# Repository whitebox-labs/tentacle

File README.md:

# Whitebox Labs Tentacle Shield for Arduino
`Models T1.15A, T1.16`

## What's the Tentacle Shield?
An Arduino shield to host and individually isolate up to 4 EZO Circuits from Atlas Scientific to measure PH, Dissolved Oxygen, Electric Conductivity (E.C.), Oxidation-Reduction Potential (ORP) and RTD (Temperature).

* 4 channels
* 5V only

Individually isolated measurement circuits and communication lines prevent noise and ground loops for precise measurements even in closed-loop systems.

## Getting Started
* [Documentation Site](https://www.whiteboxes.ch/docs/tentacle/t1)
* Download the [Setup Sketch](https://raw.githubusercontent.com/whitebox-labs/tentacle-examples/master/arduino/tentacle-setup/tentacle_setup/tentacle_setup.ino)
* [Quick Start Tutorial](https://www.whiteboxes.ch/docs/tentacle/t1/#/quickstart)

## Code Examples
* [Continuous readings](https://www.whiteboxes.ch/docs/tentacle/t1/#/continuous-example)
* [Continuous, asynchronous readings](https://www.whiteboxes.ch/docs/tentacle/t1/#/asynchronous-example)
* [Interactive, bidirectional communications](https://www.whiteboxes.ch/docs/tentacle/t1/#/interactive-example)
* [Examples Git Repository](https://github.com/whitebox-labs/tentacle-examples) `git clone https://github.com/whitebox-labs/tentacle-examples.git`
* [Download all examples (zip)](https://github.com/whitebox-labs/tentacle-examples/archive/master.zip)

## Downloads
* [Tentacle Setup sketch](https://raw.githubusercontent.com/whitebox-labs/tentacle-examples/master/arduino/tentacle-setup/tentacle_setup/tentacle_setup.ino)
* [T1.16 3D-Model (STL)](https://github.com/whitebox-labs/tentacle/blob/master/hardware/mechanical/tentacle_t1.STL)
* [T1.16 3D-Model (STEP)](https://github.com/whitebox-labs/tentacle/blob/master/hardware/mechanical/tentacle_t1.STEP)
* [T1.16 Mechanical Drawing (PDF)](https://github.com/whitebox-labs/tentacle/raw/master/hardware/mechanical/tentacle_t1_mechanical.pdf)
* [BNC Connector Mechanical Drawing (PDF)](https://github.com/whitebox-labs/tentacle/raw/master/hardware/mechanical/bnc_mechanical.pdf)
* [T1.16 Schematic (PDF)](https://github.com/whitebox-labs/tentacle/raw/master/hardware/tentacle_schematic.pdf)

## Support
For customer support, please use the [contact form](https://www.whiteboxes.ch/contact/) on our website.

If you find bug in the documentation, examples or the schematic, feel free to create an issue or even a pull request here on GitHub. 

## Open Source
The Tentacle Shield is [certified](http://certificate.oshwa.org/certification-directory/) Open Source Hardware with UID CH000003. Schematics and layout are licensed under [Creative Commons BY-SA 4.0](http://creativecommons.org/licenses/by-sa/4.0/). Silkscreen graphics and the trade mark “Tentacle” are intellectual property of Whitebox Labs

* [Hardware source files on GitHub](https://github.com/whitebox-labs/tentacle) `git clone https://github.com/whitebox-labs/tentacle.git`

Made with 

## Buy
* From [our store](https://www.whiteboxes.ch/) – we ship worldwide
* or from one of our [Distributors](https://www.whiteboxes.ch/distributors)

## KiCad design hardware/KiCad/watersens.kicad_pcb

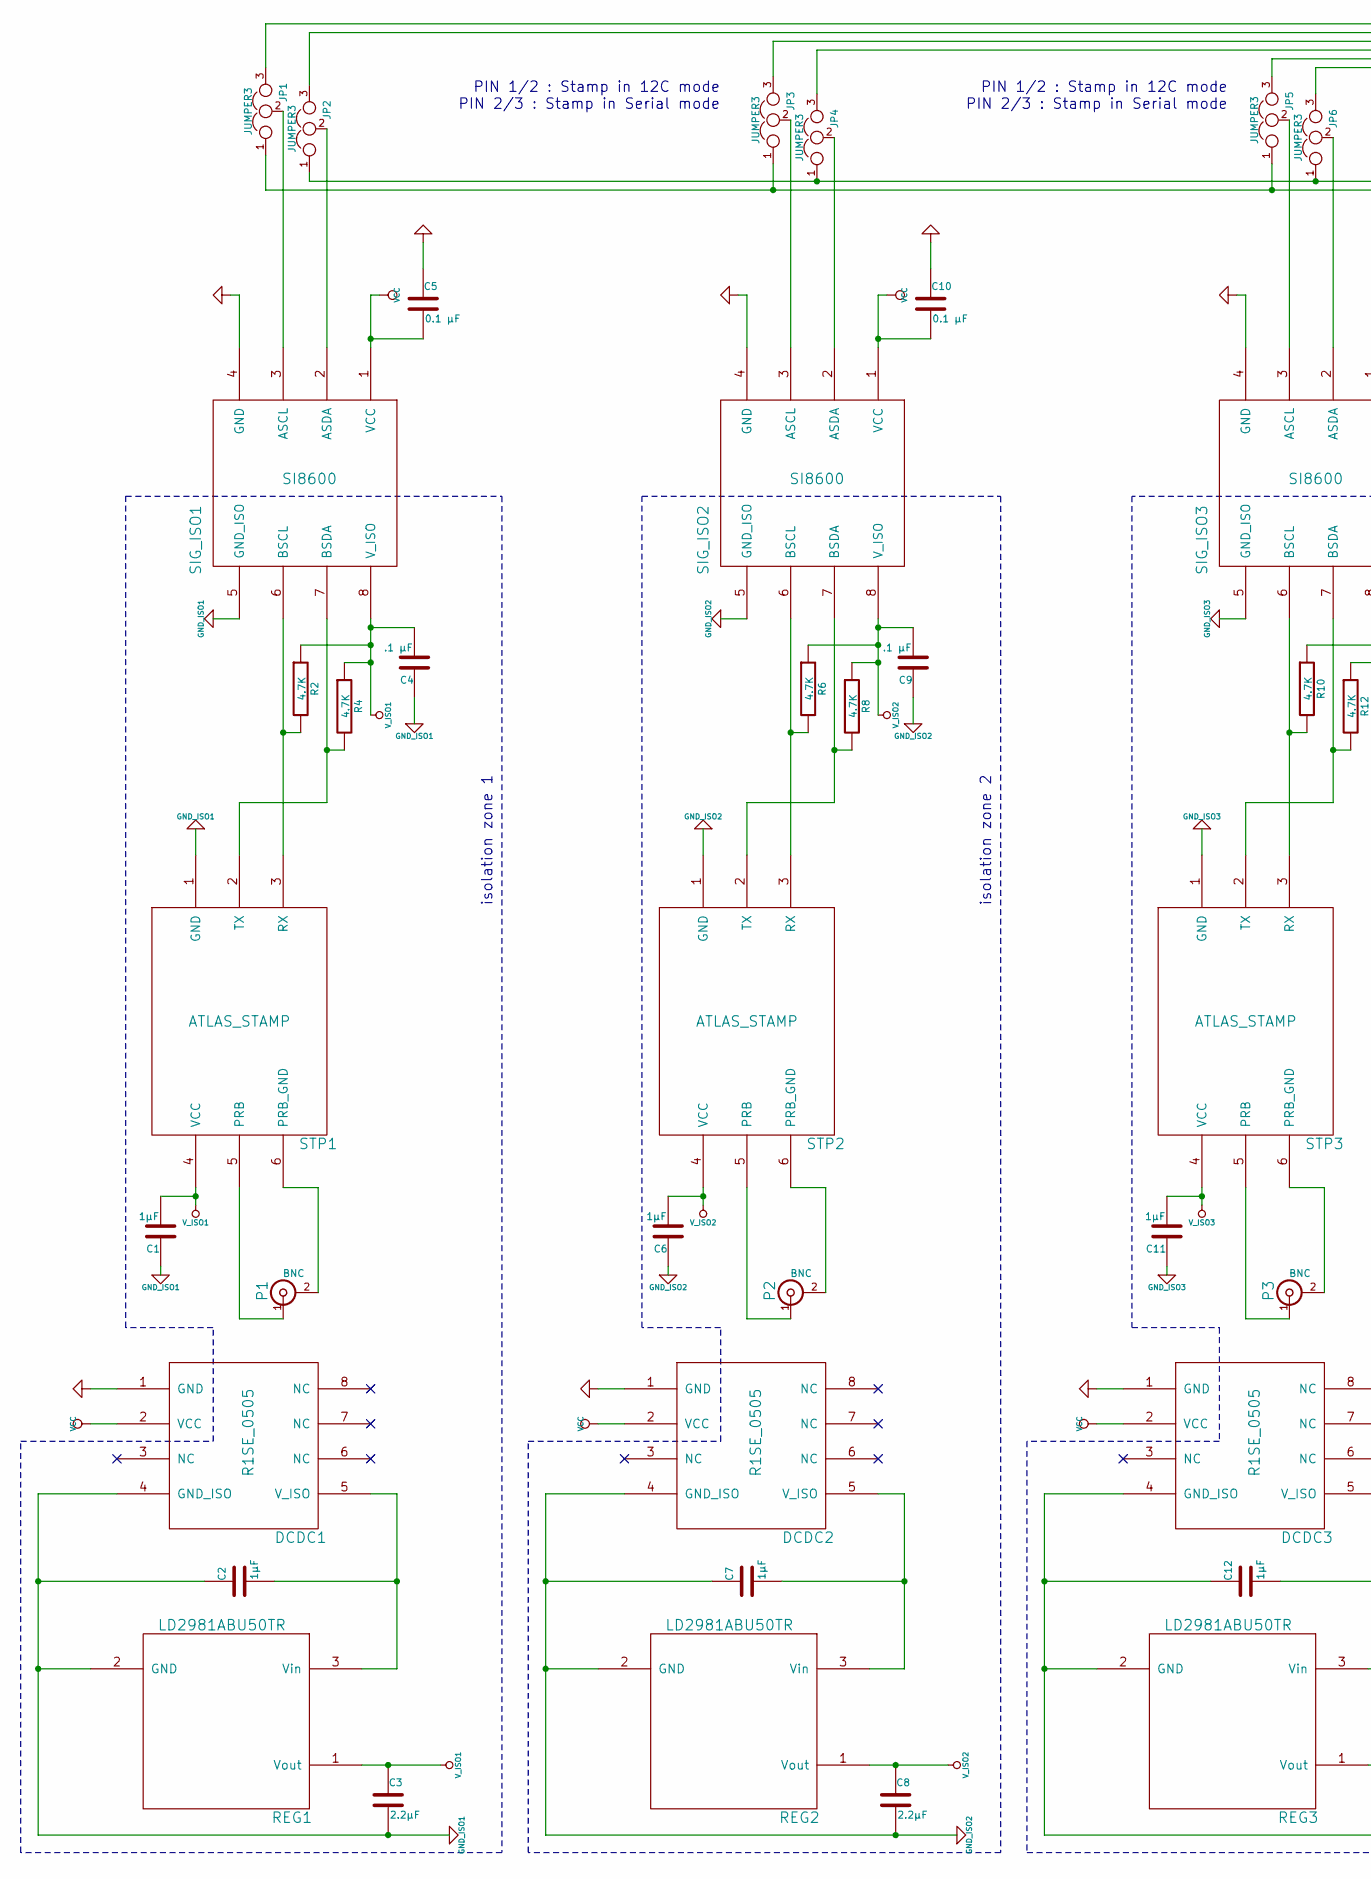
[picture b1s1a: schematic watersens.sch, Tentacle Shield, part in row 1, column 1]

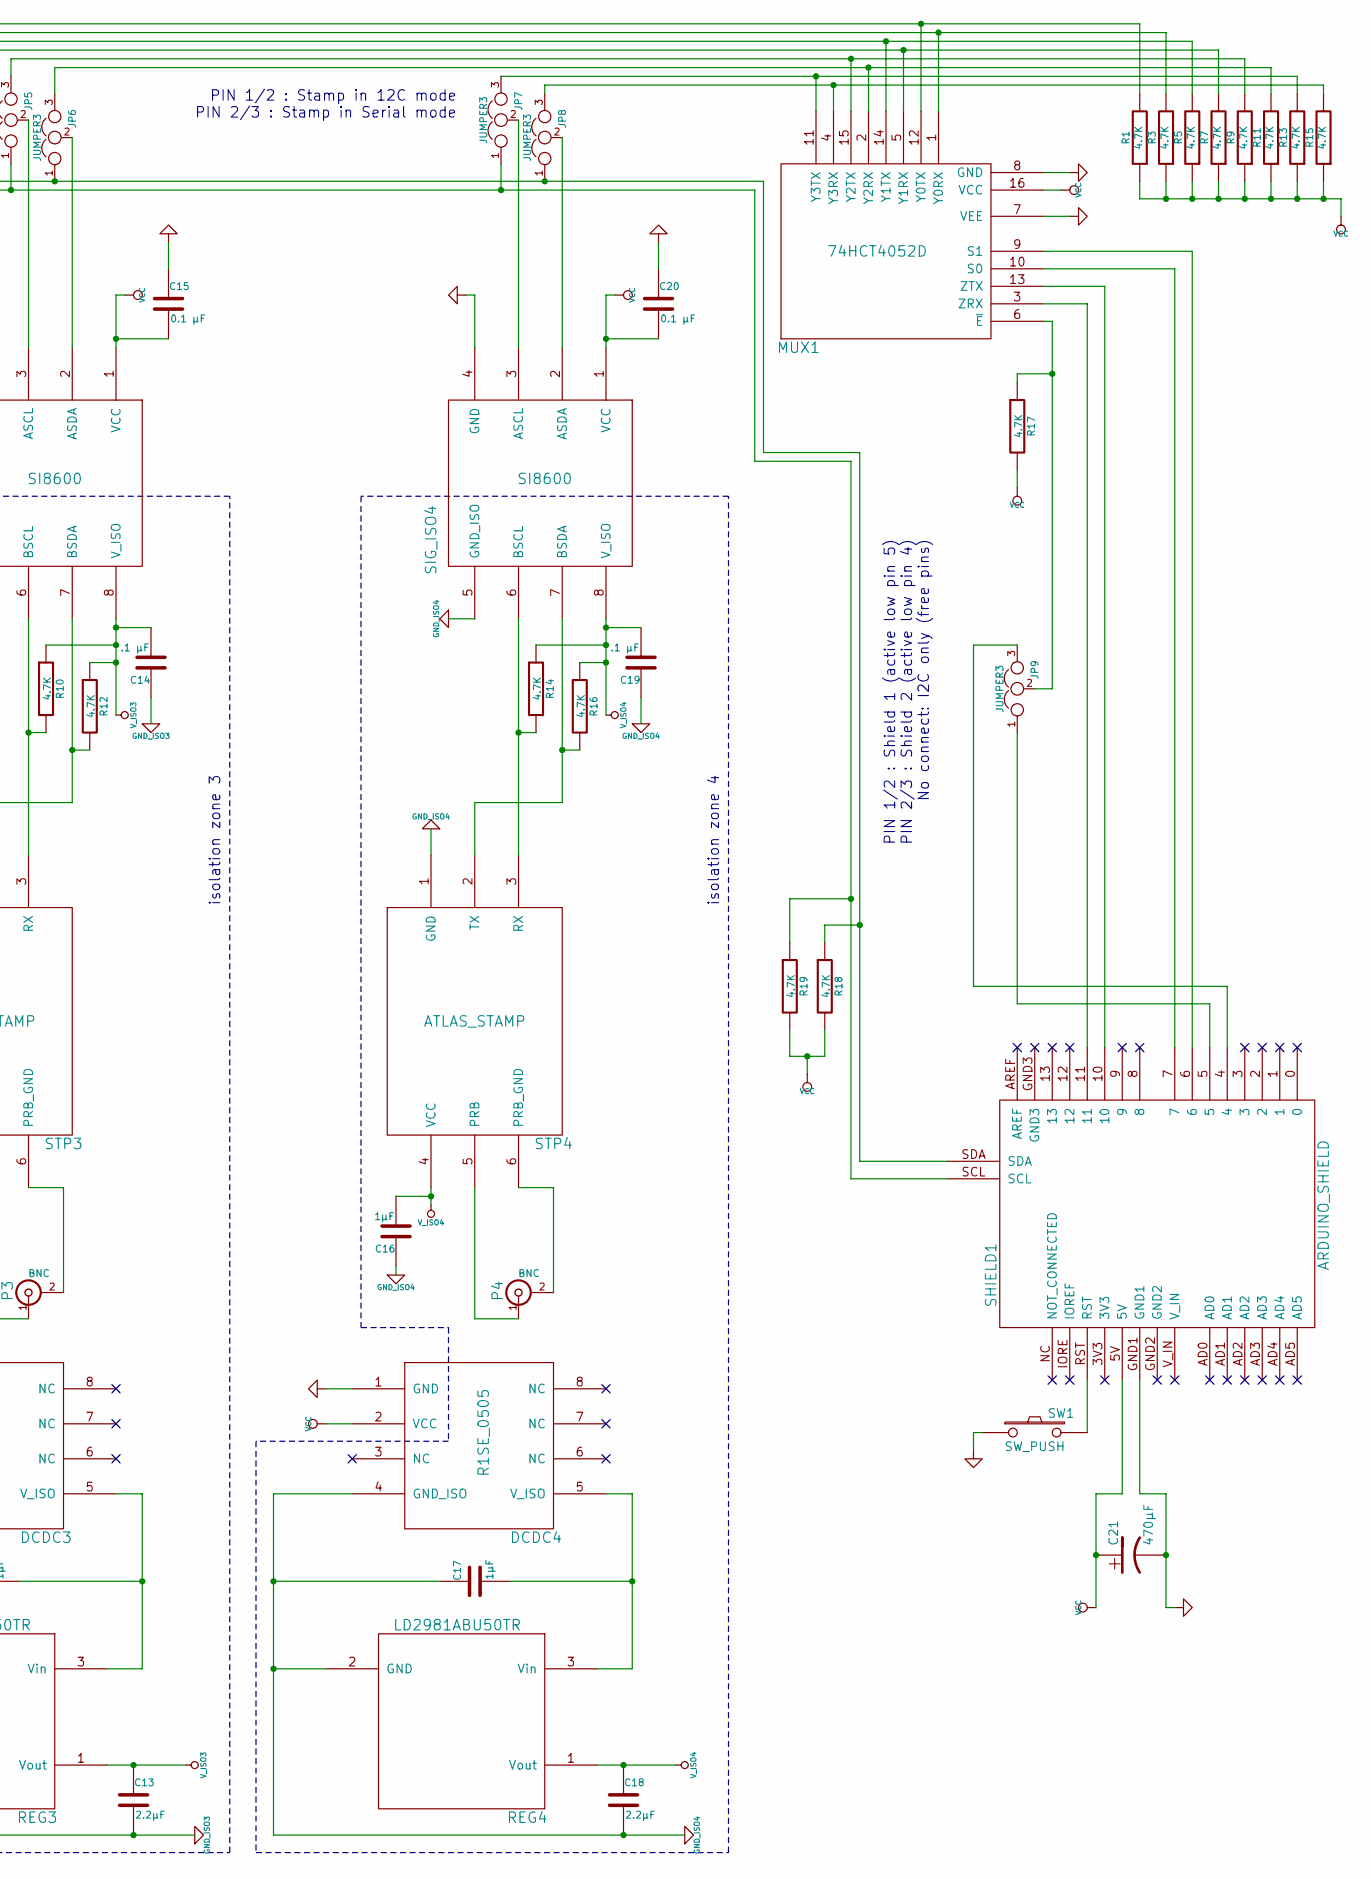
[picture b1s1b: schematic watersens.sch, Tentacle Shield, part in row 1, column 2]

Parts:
C1, C6, C11, C16: 1µF; SM0805a
C2, C7, C12, C17: 1µF; SM0805
C3, C8, C13, C18: 2.2µF; SM0805
C4, C9, C14, C19: .1 µF; SM0805a
C5, C10, C15, C20: 0.1 µF; SM0805a
C21: 470µF; c_tant_X
DCDC1, DCDC2, DCDC3, DCDC4: R1SE_0505
JP1, JP2, JP3, JP4, JP5, JP6, JP7, JP8, JP9: JUMPER3; PINHEAD1-3a
MUX1: 74HCT4052D; SO16N
P1, P2, P3, P4: BNC; BNC-1337543a
R1, R2, R3, R4, R5, R6, R7, R8, R9, R10, R11, R12, R13, R14, R15, R16, R18, R19: 4.7K; SM0805a
R17: 4.7K; SM0805
REG1, REG2, REG3, REG4: LD2981ABU50TR; sot89
SHIELD1: ARDUINO_SHIELD; ARDUINO_SHIELD_040pinsa_no_outline
SIG_ISO1, SIG_ISO2, SIG_ISO3, SIG_ISO4: SI8600; so-8a
STP1, STP2, STP3, STP4: ATLAS_STAMP; Atlas_Stamp
SW1: SW_PUSH; B3S-1000P

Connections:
GND: C5.1, C10.1, C15.1, C20.1, C21.2, DCDC1.1 (GND), DCDC2.1 (GND), DCDC3.1 (GND), DCDC4.1 (GND), MUX1.7 (VEE), MUX1.8 (GND), SHIELD1.GND1, SIG_ISO1.4 (GND), SIG_ISO2.4 (GND), SIG_ISO3.4 (GND), SIG_ISO4.4 (GND), SW1.1
GND_ISO1: C1.1, C2.1, C3.2, C4.1, DCDC1.4 (GND_ISO), REG1.2 (GND), SIG_ISO1.5 (GND_ISO), STP1.1 (GND)
GND_ISO2: C6.1, C7.1, C8.2, C9.1, DCDC2.4 (GND_ISO), REG2.2 (GND), SIG_ISO2.5 (GND_ISO), STP2.1 (GND)
GND_ISO3: C11.1, C12.1, C13.2, C14.1, DCDC3.4 (GND_ISO), REG3.2 (GND), SIG_ISO3.5 (GND_ISO), STP3.1 (GND)
GND_ISO4: C16.1, C17.1, C18.2, C19.1, DCDC4.4 (GND_ISO), REG4.2 (GND), SIG_ISO4.5 (GND_ISO), STP4.1 (GND)
unnamed: C2.2, DCDC1.5 (V_ISO), REG1.3 (Vin)
unnamed: C7.2, DCDC2.5 (V_ISO), REG2.3 (Vin)
unnamed: C12.2, DCDC3.5 (V_ISO), REG3.3 (Vin)
unnamed: C17.2, DCDC4.5 (V_ISO), REG4.3 (Vin)
unnamed: JP1.1, JP3.1, JP5.1, JP7.1, R19.1, SHIELD1.SCL
unnamed: JP1.2, SIG_ISO1.3 (ASCL)
unnamed: JP1.3, MUX1.12 (Y0TX), R1.2
unnamed: JP2.1, JP4.1, JP6.1, JP8.1, R18.1, SHIELD1.SDA
unnamed: JP2.2, SIG_ISO1.2 (ASDA)
unnamed: JP2.3, MUX1.1 (Y0RX), R3.2
unnamed: JP3.2, SIG_ISO2.3 (ASCL)
unnamed: JP3.3, MUX1.14 (Y1TX), R5.2
unnamed: JP4.2, SIG_ISO2.2 (ASDA)
unnamed: JP4.3, MUX1.5 (Y1RX), R7.2
unnamed: JP5.2, SIG_ISO3.3 (ASCL)
unnamed: JP5.3, MUX1.15 (Y2TX), R9.2
unnamed: JP6.2, SIG_ISO3.2 (ASDA)
unnamed: JP6.3, MUX1.2 (Y2RX), R11.2
unnamed: JP7.2, SIG_ISO4.3 (ASCL)
unnamed: JP7.3, MUX1.11 (Y3TX), R13.2
unnamed: JP8.2, SIG_ISO4.2 (ASDA)
unnamed: JP8.3, MUX1.4 (Y3RX), R15.2
unnamed: JP9.1, SHIELD1.5
unnamed: JP9.2, MUX1.6 (~E), R17.1
unnamed: JP9.3, SHIELD1.4
unnamed: MUX1.3 (ZRX), SHIELD1.11
unnamed: MUX1.9 (S1), SHIELD1.6
unnamed: MUX1.10 (S0), SHIELD1.7
unnamed: MUX1.13 (ZTX), SHIELD1.10
unnamed: P1.1 (In), STP1.5 (PRB)
unnamed: P1.2 (Ext), STP1.6 (PRB_GND)
unnamed: P2.1 (In), STP2.5 (PRB)
unnamed: P2.2 (Ext), STP2.6 (PRB_GND)
unnamed: P3.1 (In), STP3.5 (PRB)
unnamed: P3.2 (Ext), STP3.6 (PRB_GND)
unnamed: P4.1 (In), STP4.5 (PRB)
unnamed: P4.2 (Ext), STP4.6 (PRB_GND)
unnamed: R2.2, SIG_ISO1.6 (BSCL), STP1.3 (RX)
unnamed: R4.2, SIG_ISO1.7 (BSDA), STP1.2 (TX)
unnamed: R6.2, SIG_ISO2.6 (BSCL), STP2.3 (RX)
unnamed: R8.2, SIG_ISO2.7 (BSDA), STP2.2 (TX)
unnamed: R10.2, SIG_ISO3.6 (BSCL), STP3.3 (RX)
unnamed: R12.2, SIG_ISO3.7 (BSDA), STP3.2 (TX)
unnamed: R14.2, SIG_ISO4.6 (BSCL), STP4.3 (RX)
unnamed: R16.2, SIG_ISO4.7 (BSDA), STP4.2 (TX)
unnamed: SHIELD1.RST, SW1.2
VCC: C5.2, C10.2, C15.2, C20.2, C21.1, DCDC1.2 (VCC), DCDC2.2 (VCC), DCDC3.2 (VCC), DCDC4.2 (VCC), MUX1.16 (VCC), R1.1, R3.1, R5.1, R7.1, R9.1, R11.1, R13.1, R15.1, R17.2, R18.2, R19.2, SHIELD1.5V, SIG_ISO1.1 (VCC), SIG_ISO2.1 (VCC), SIG_ISO3.1 (VCC), SIG_ISO4.1 (VCC)
V_ISO1: C1.2, C3.1, C4.2, R2.1, R4.1, REG1.1 (Vout), SIG_ISO1.8 (V_ISO), STP1.4 (VCC)
V_ISO2: C6.2, C8.1, C9.2, R6.1, R8.1, REG2.1 (Vout), SIG_ISO2.8 (V_ISO), STP2.4 (VCC)
V_ISO3: C11.2, C13.1, C14.2, R10.1, R12.1, REG3.1 (Vout), SIG_ISO3.8 (V_ISO), STP3.4 (VCC)
V_ISO4: C16.2, C18.1, C19.2, R14.1, R16.1, REG4.1 (Vout), SIG_ISO4.8 (V_ISO), STP4.4 (VCC)

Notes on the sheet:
PIN 1/2 : Shield 1 (active low pin 5) PIN 2/3 : Shield 2 (active low pin 4) No connect: I2C only (free pins)
PIN 1/2 : Stamp in 12C mode PIN 2/3 : Stamp in Serial mode
isolation zone 1
isolation zone 2
isolation zone 3
isolation zone 4

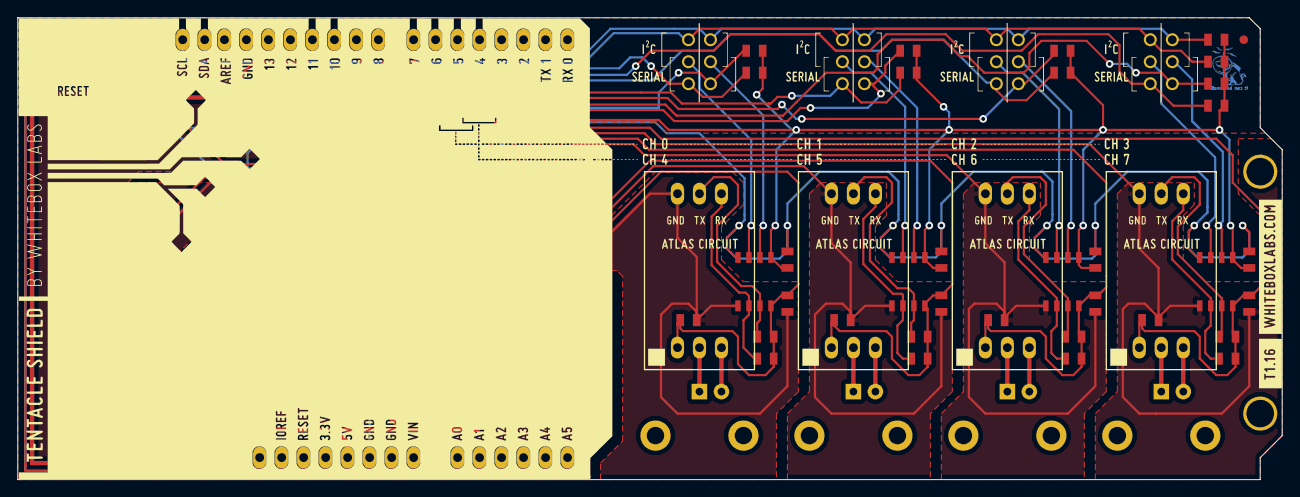
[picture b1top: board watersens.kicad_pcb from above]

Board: 2 copper layers, 146.1 x 53.3 mm, 77 parts (0 on the bottom side), 56 nets.

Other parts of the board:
VAL: REF; 141029_back_V2_highres_B.SilkS_146mm_flipped
VAL#2: REF; icon
VAL#3: REF; 141029_front_V3_highres_F.SilkS_146mm
fiducial: VAL**; fiducial
fiducial#2: VAL**; fiducial

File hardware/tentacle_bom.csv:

Id,Description,Package,Qty,Designator,Designation
1,1x6-pin female header .1inch,.1 inch header,1,SHIELD1,ARDUINO_SHIELD
2,1x8-pin female header .1inch,.1 inch header,2,SHIELD1,ARDUINO_SHIELD
3,1x10-pin female header .1inch,.1 inch header,1,SHIELD1,ARDUINO_SHIELD
4,LDO voltage regulator,SOT89,4,"REG1,REG2,REG3,REG4",LD2981ABU50TR
5,UART multiplexer,SO16N,1,MUX1,74HCT4052D122
6,Digital signal isolator,so-8,4,"SIG_ISO2,SIG_ISO3,SIG_ISO4,SIG_ISO1",SI8600
7,"SMD resistor 4.7K, 1/8W",SM0805,19,"R16,R14,R12,R10,R8,R6,R4,R2,R17,R3,R1,R7,R5,R9,R11,R13,R15,R18,R19",4.7K
8,Multilayer Ceramic Capacitor 0.1uF,SM0805,8,"C4,C9,C14,C19,C10,C5,C15,C20",0.1 µF
9,Multilayer Ceramic Capacitor 1uF,SM0805,8,"C12,C2,C7,C17,C1,C6,C11,C16",1µF
10,Multilayer Ceramic Capacitor 2.2uF,SM0805,4,"C3,C8,C13,C18",2.2µF
11,Tantalum Capacitor 470uF,c_tant_x,1,C21,470µF
12,1x3 male pin headers .1inch,1x3  .1 inch spacing male pin,1,JP9,JUMPER3
13,2x3 male pin headers .1inch,2x3  .1 inch spacing male pin,4,"JP1,JP3,JP5,JP7,JP2,JP4,JP6,JP8",JUMPER3
14,Tactile push button,B3S-1000P,1,SW1,SW_PUSH
15,Isolated DC/DC converter 5V,R1SE_0505,4,"DCDC1,DCDC2,DCDC3,DCDC4",R1SE_0505
16,BNC Connector,BNC-1337542,4,"P1,P2,P3,P4",BNC
17,1x3-pin female header .1inch,1x3  .1 inch spacing female pin,8,"STP1,STP2,STP3,STP4",ATLAS_STAMP
18,Shorting jumper .1inch,.1 inch jumper,9,JP*,"JUMPER, JUMPER3"

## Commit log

2015-06-16 adding readme
2015-06-16 added link to examples
2015-06-16 basic readme stuff
2015-06-17 minor readme changes
2015-06-17 removed old arduino module
2015-06-17 remove lib reference to arduino V3 folder
    update libs, regen net list, resync along the eeschema-netlist-PCBnew
    chain.
2015-06-17 updated schematic pdf
2015-06-17 update schema/rename bom
2015-06-17 removed double schematic pdf
2015-06-30 added "issue policy"
2015-07-15 short pin 7 on mux to ground.
    update schematic, netlist, PCB, fills, and plots.
2015-07-15 update component lib pin labels
    update labels, update to chain.
2015-08-24 fixed problem with i2c commands that take longer than expected. and some formatting clean-up
2015-08-24 added missing semicolon
2015-08-24 renamed sketch
2015-08-24 added simple uart example
2015-08-24 comment cleanup
2015-08-27 renamed sftSerial to sSerial
2015-08-27 renamed myserial to sSerial
2015-08-27 radically removed stuff to make it simpler.
    reverted to "atlas scientific example style" commands
    (<channel>:<command>). removed help and other stuff. fixed i2c
    command-pending issue. fixed formatting.
2015-08-27 Rename examples/simple_console/simple_console.ino to examples/mixed_uart_i2c/mixed_uart_i2c.ino
2015-08-28 Rename examples/simple_uart/simple_uart.ino to examples/uart_only/uart_only.ino
2015-08-28 made i2c stati more verbose
2015-08-28 added a i2c-only example
2015-08-28 added an image and other minor changes
2015-08-28 fixed header comments
2015-10-12 netlist
    I re-added the netlist from backup
    removed *.net from .gitignore
    netlist needed to link schmatic to pcb design
2015-10-16 T1.16
    added art, removed edges from shield mod SilkS, added previews
2015-10-17 removed silkscreen from components
2015-10-29 cleaned up gerber files structure.
2015-11-19 removed unused varuable "received_from_computer" and fixed a problem with DO probe auto-detection
2015-11-19 initial port to the Yun
2015-11-23 added command "scani2c" to scan i2c devices only. added license. updated usage instructions.
2015-11-23 added license. updated usage instructions.
2015-11-23 added command "scani2c" to scan for i2c devices only. added license. updated usage instructions. changed host baudrate to 9600. cleanup.
2015-11-23 removed unused variable "received_from_computer"
2015-11-23 cleanup
2015-11-23 added intro message
2015-11-23 added examples for Arduino Yun
2015-11-25 fixed compile errors
2015-11-27 changed pin definitions in schematic parts
    changed pin definitions in schematic parts metadata for improved error
    checking,
2015-12-07 fixed comments and usage instructions
2015-12-07 added asynchronous example
2015-12-07 changed sketch to use 4 circuits. updated IDs to use circuit factory settings.
2015-12-08 changed reading delay to 1000ms
2015-12-08 replaced a String by *char[]
2015-12-08 yun version of asynchronous example
2015-12-08 fab file
    .pos file added to gerbs folder
    -drills/positioning origin set to lower left feducial
    -regen gerbs, drills and .pos
    -.pos settings : mm scale, 1 file per board, no force
2015-12-08 drastically simplified. continuous sensor readings.
2015-12-08 comments & formatting
2015-12-08 comments
2015-12-08 simplified code, continuous readings, updated comments
2015-12-12 return "success" instead of "ack" on successful i2c command
2015-12-13 added IoT example: Initial State
2015-12-14 UART asynchronous example
2015-12-14 renamed TOTAL_CIRCUITS to NUM_CIRCUITS
2015-12-14 reorganized and renamed example file structure
2015-12-14 more re-organizing
2015-12-14 fixed comments and changed default baudrate to 38400
2015-12-14 simplified mixed-mode examples & updated comments
2015-12-14 added I2C-only interactive example
2015-12-14 updated comments
2015-12-15 update pos file
    -update the attributes of SMD footprints to 'Normal + Insert'
    -update module lib files.
    -regen gerbs, drills and pos files
    -checked for other parts with missing attributes. C_tant_x SWx and DCDCx
    corrected.
2015-12-15 fixed UART communication to work with old or slow circuits
2016-01-08 setup tool for SAM based arduinos (Zero, Due, etc) only for Tentacle Mini
2016-04-09 removed serialEvent(). Leonardo, Yun, Due now compatible (+ uno, mega...)
2016-05-09 working on SAM / 101 compatibility
2016-05-09 added EZO RTD to the auto-detection. fixed circuit names.
2016-05-10 compatibility optimizations
    tested to work with
    T1: UNO, Mega, leonardo, yun
    T2: UNO, Mega, leonardo, yun, Zero
    Note: not compatible with Arduino 101.
2016-05-10 removed argument
2016-09-18 Update for KiCad v4
2016-09-18 Remove files no longer used
2016-09-18 Regenerate gerber files
2016-09-18 Use 'tentacle' github footprint library
2016-09-18 updated link to examples repo
2016-09-18 added osx dust to gitignore
2016-09-18 examples have moved to https://github.com/whitebox-labs/tentacle-examples
2016-09-18 examples moved to new repo
2017-08-21 added detailed 2d-drawing and 3d model
2017-08-21 added detail drawing for BNC connectors
2017-08-21 updated BOM
2018-08-23 added documentation media
2018-08-23 smaller KiCAD icon
2018-08-23 adding documentation media
2018-08-23 add documentation media
2018-08-23 docs media
2018-08-23 rename
2018-08-23 doc media
2018-08-24 added markdown documentation
2018-08-24 moved docs to separate repo
2018-08-24 added STEP 3D-model
2018-09-21 zipped STEP model for easier download
2021-11-09 Update README.md
    https://forum.kicad.info/t/warning-avoid-all-links-to-kicad-pcb-org-use-kicad-org/31521
